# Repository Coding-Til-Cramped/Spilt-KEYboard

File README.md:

# Split keyboard

My Split Keyboar has 41 keys that are controlled by 2 XIAO-nRF52840 because of their bluetooth, this keyboard will run on ZMK firmware

I will use it as my main keboard for my laptop that is why the bloototh was needed because i do not have many ports 

# Features

42 fully customisable keys

Bluetooth conectivity 

Great sounding Cherry MX blue Switches

# CAD

I am planning on designing a case onece i know the pcb model will work it will have wrist rests and slightly tillted 

Here is My PCB for a rough idea of the shape:

# PCB

This is my PCB it is my second PCB in kicad and i think i have become a lot more efficient and it is a lot more organized

SCHEMATIC:

This is my PCB layout, i tried to make it look like some ergonomic split keyboard that i saw online and this is what i came up with 

PCB:

# Firmware 

I am using ZMK firmware as it seems to be the go to for custom keyboards

# BOM (not final checking on the slack)

2x Seeed Studio XIAO nRF52840

42x MX-style mechanical switches

42x MX compatible white keycaps

42x SMD diodes – 1N4148 (SOD-123)

2x Li-Po battery, 3.7 V (JST-PH 2-pin)

2x 802 kΩ resistor (0603)

2x 2 MΩ resistor (0603)

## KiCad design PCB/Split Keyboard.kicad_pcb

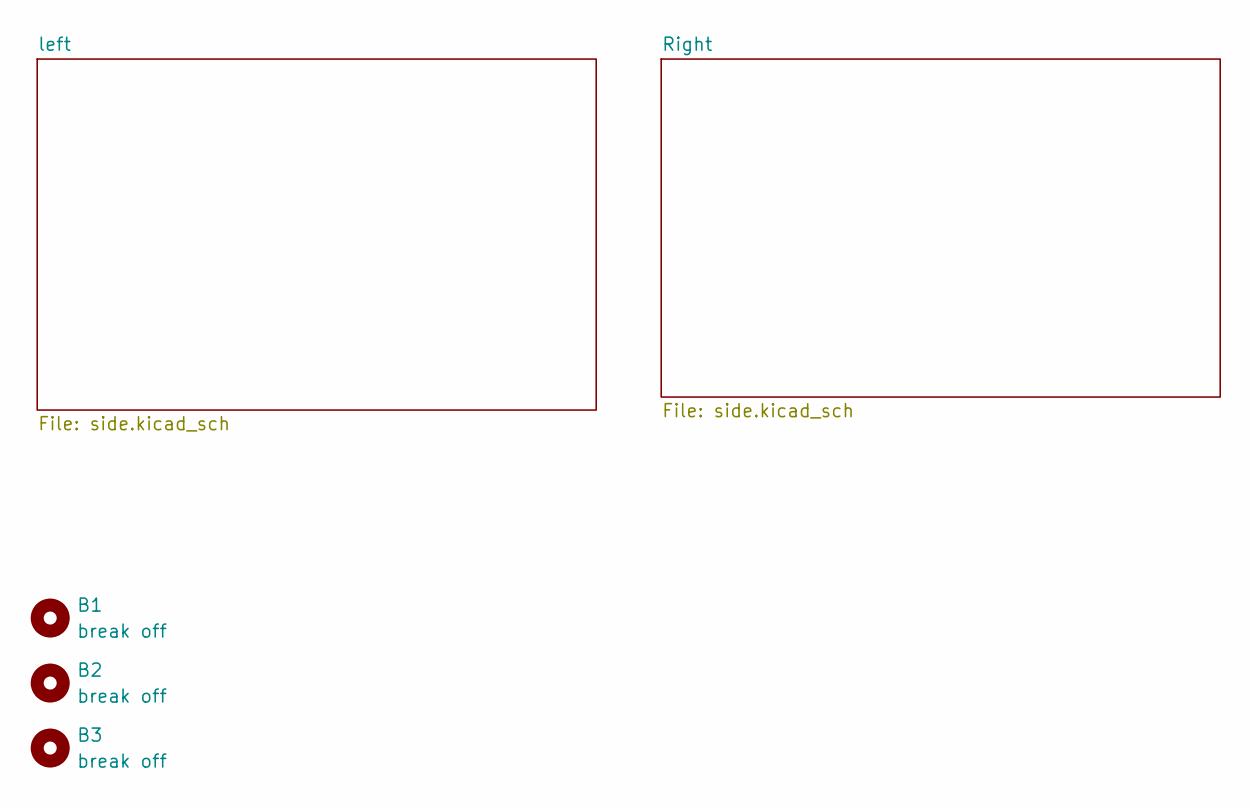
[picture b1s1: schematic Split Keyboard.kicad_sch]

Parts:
B1, B2, B3: break off; mousebites_5p5mm_easysnap

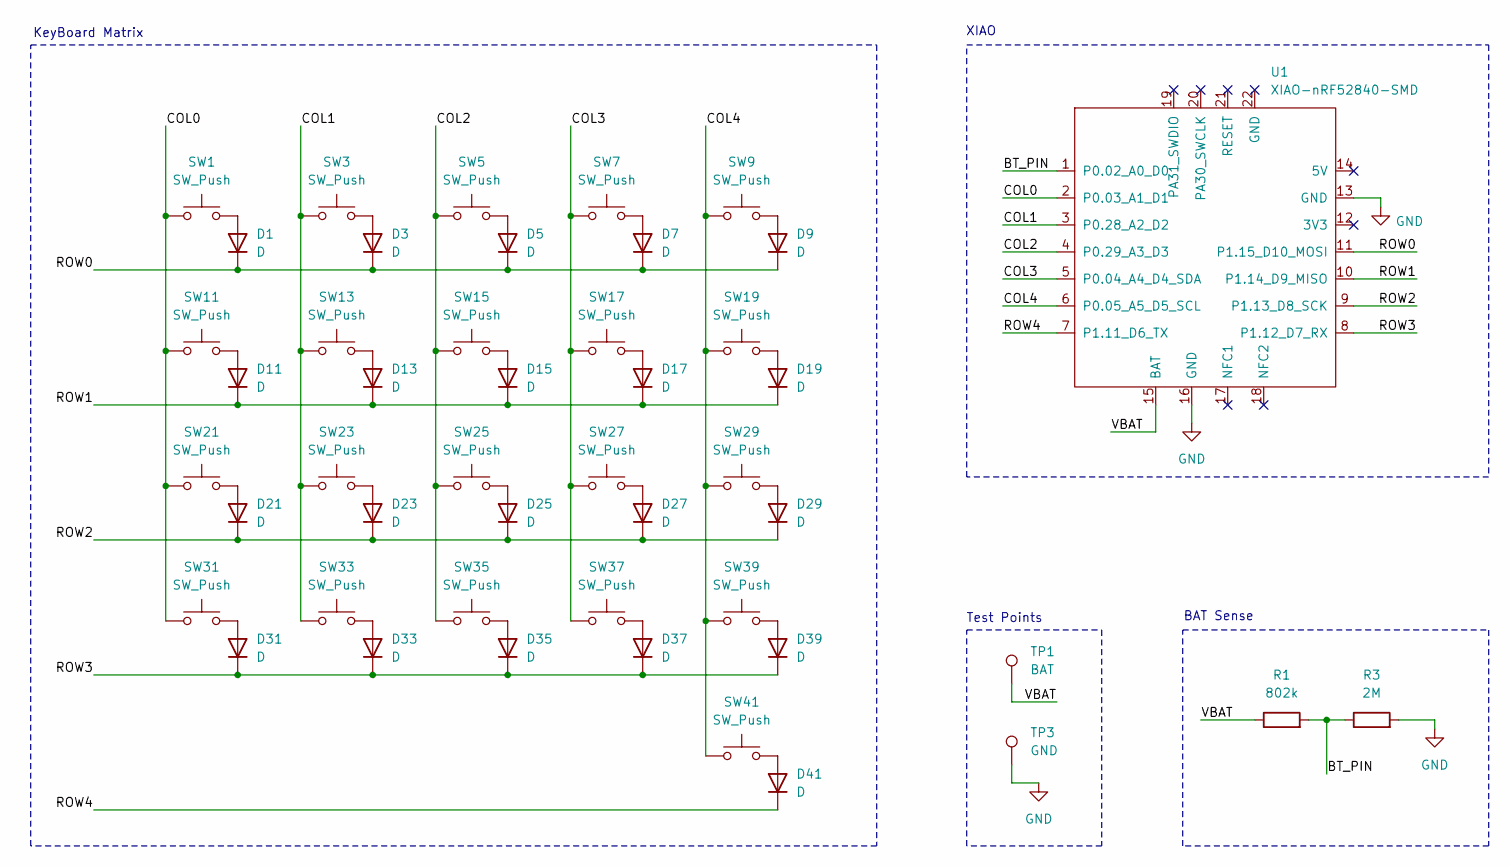
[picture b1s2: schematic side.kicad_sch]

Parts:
D1, D3, D5, D7, D9, D11, D13, D15, D17, D19, D21, D23, D25, D27, D29, D31, D33, D35, D37, D39, D41: D; D_SOD-123
R1: 802k; R_0805_2012Metric
R3: 2M; R_0805_2012Metric
SW1, SW3, SW5, SW7, SW9, SW11, SW13, SW15, SW17, SW19, SW21, SW23, SW25, SW27, SW29, SW31, SW33, SW35, SW37, SW39, SW41: SW_Push; SW_Cherry_MX_1.00u_PCB
TP1: BAT; TestPoint_Pad_D2.0mm
TP3: GND; TestPoint_Pad_D2.0mm
U1: XIAO-nRF52840-SMD; modified-XIAO-nRF52840-SMD

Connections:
/left/BT_PIN: R1.2, R3.1, U1.1 (P0.02_A0_D0)
/left/COL0: SW1.1, SW11.1, SW21.1, SW31.1, U1.2 (P0.03_A1_D1)
/left/COL1: SW3.1, SW13.1, SW23.1, SW33.1, U1.3 (P0.28_A2_D2)
/left/COL2: SW5.1, SW15.1, SW25.1, SW35.1, U1.4 (P0.29_A3_D3)
/left/COL3: SW7.1, SW17.1, SW27.1, SW37.1, U1.5 (P0.04_A4_D4_SDA)
/left/COL4: SW9.1, SW19.1, SW29.1, SW39.1, SW41.1, U1.6 (P0.05_A5_D5_SCL)
/left/ROW0: D1.1 (K), D3.1 (K), D5.1 (K), D7.1 (K), D9.1 (K), U1.11 (P1.15_D10_MOSI)
/left/ROW1: D11.1 (K), D13.1 (K), D15.1 (K), D17.1 (K), D19.1 (K), U1.10 (P1.14_D9_MISO)
/left/ROW2: D21.1 (K), D23.1 (K), D25.1 (K), D27.1 (K), D29.1 (K), U1.9 (P1.13_D8_SCK)
/left/ROW3: D31.1 (K), D33.1 (K), D35.1 (K), D37.1 (K), D39.1 (K), U1.8 (P1.12_D7_RX)
/left/ROW4: D41.1 (K), U1.7 (P1.11_D6_TX)
/left/VBAT: R1.1, TP1.1, U1.15 (BAT)
GND: R3.2, TP3.1, U1.13 (GND), U1.16 (GND); also elsewhere on the board
unnamed: D1.2 (A), SW1.2
unnamed: D3.2 (A), SW3.2
unnamed: D5.2 (A), SW5.2
unnamed: D7.2 (A), SW7.2
unnamed: D9.2 (A), SW9.2
unnamed: D11.2 (A), SW11.2
unnamed: D13.2 (A), SW13.2
unnamed: D15.2 (A), SW15.2
unnamed: D17.2 (A), SW17.2
unnamed: D19.2 (A), SW19.2
unnamed: D21.2 (A), SW21.2
unnamed: D23.2 (A), SW23.2
unnamed: D25.2 (A), SW25.2
unnamed: D27.2 (A), SW27.2
unnamed: D29.2 (A), SW29.2
unnamed: D31.2 (A), SW31.2
unnamed: D33.2 (A), SW33.2
unnamed: D35.2 (A), SW35.2
unnamed: D37.2 (A), SW37.2
unnamed: D39.2 (A), SW39.2
unnamed: D41.2 (A), SW41.2

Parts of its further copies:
D2, D4, D6, D8, D10, D12, D14, D16, D18, D20, D22, D24, D26, D28, D30, D32, D34, D36, D38, D40, D42: D; D_SOD-123
R2: 802k; R_0805_2012Metric
R4: 2M; R_0805_2012Metric
SW2, SW4, SW6, SW8, SW10, SW12, SW14, SW16, SW18, SW20, SW22, SW24, SW26, SW28, SW30, SW32, SW34, SW36, SW38, SW40, SW42: SW_Push; SW_Cherry_MX_1.00u_PCB
TP2: BAT; TestPoint_Pad_D2.0mm
TP4: GND; TestPoint_Pad_D2.0mm
U2: XIAO-nRF52840-SMD; modified-XIAO-nRF52840-SMD

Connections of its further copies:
/Right/BT_PIN: R2.2, R4.1, U2.1 (P0.02_A0_D0)
/Right/COL0: SW2.1, SW12.1, SW22.1, SW32.1, U2.2 (P0.03_A1_D1)
/Right/COL1: SW4.1, SW14.1, SW24.1, SW34.1, U2.3 (P0.28_A2_D2)
/Right/COL2: SW6.1, SW16.1, SW26.1, SW36.1, U2.4 (P0.29_A3_D3)
/Right/COL3: SW8.1, SW18.1, SW28.1, SW38.1, U2.5 (P0.04_A4_D4_SDA)
/Right/COL4: SW10.1, SW20.1, SW30.1, SW40.1, SW42.1, U2.6 (P0.05_A5_D5_SCL)
/Right/ROW0: D2.1 (K), D4.1 (K), D6.1 (K), D8.1 (K), D10.1 (K), U2.11 (P1.15_D10_MOSI)
/Right/ROW1: D12.1 (K), D14.1 (K), D16.1 (K), D18.1 (K), D20.1 (K), U2.10 (P1.14_D9_MISO)
/Right/ROW2: D22.1 (K), D24.1 (K), D26.1 (K), D28.1 (K), D30.1 (K), U2.9 (P1.13_D8_SCK)
/Right/ROW3: D32.1 (K), D34.1 (K), D36.1 (K), D38.1 (K), D40.1 (K), U2.8 (P1.12_D7_RX)
/Right/ROW4: D42.1 (K), U2.7 (P1.11_D6_TX)
/Right/VBAT: R2.1, TP2.1, U2.15 (BAT)
GND: R4.2, TP4.1, U2.13 (GND), U2.16 (GND); also elsewhere on the board
unnamed: D2.2 (A), SW2.2
unnamed: D4.2 (A), SW4.2
unnamed: D6.2 (A), SW6.2
unnamed: D8.2 (A), SW8.2
unnamed: D10.2 (A), SW10.2
unnamed: D12.2 (A), SW12.2
unnamed: D14.2 (A), SW14.2
unnamed: D16.2 (A), SW16.2
unnamed: D18.2 (A), SW18.2
unnamed: D20.2 (A), SW20.2
unnamed: D22.2 (A), SW22.2
unnamed: D24.2 (A), SW24.2
unnamed: D26.2 (A), SW26.2
unnamed: D28.2 (A), SW28.2
unnamed: D30.2 (A), SW30.2
unnamed: D32.2 (A), SW32.2
unnamed: D34.2 (A), SW34.2
unnamed: D36.2 (A), SW36.2
unnamed: D38.2 (A), SW38.2
unnamed: D40.2 (A), SW40.2
unnamed: D42.2 (A), SW42.2

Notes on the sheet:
KeyBoard Matrix
Test Points
XIAO
BAT Sense

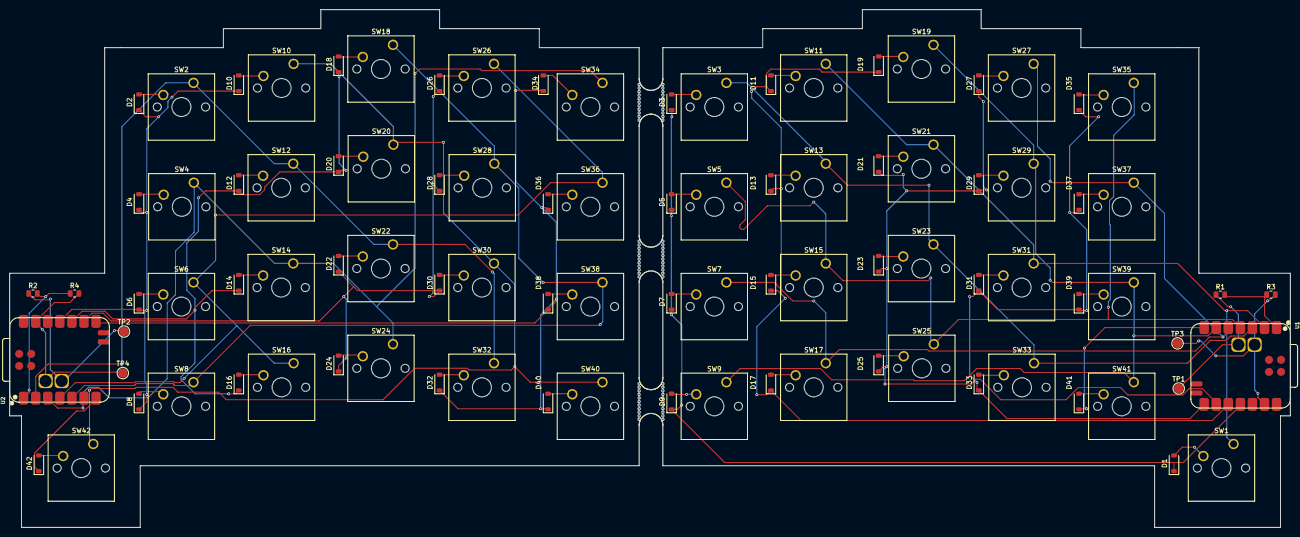
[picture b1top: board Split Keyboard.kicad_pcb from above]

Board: 2 copper layers, 269.6 x 109.0 mm, 97 parts (0 on the bottom side), 67 nets.

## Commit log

2026-01-15 main bulk of the read me
2026-01-15 firmware
2026-01-15 added images
